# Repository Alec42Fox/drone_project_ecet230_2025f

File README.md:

# ECET - 230 - 001 - HMS (Height Maintenance System)
* video of the prototype in action (fixed to a single axis)
* Also hyperlink to simulation below:

## Goals
* Make a single propelled drone that hovers at a specific height and can get back to that height when outside forces act on it.
## Team Members
* Alec Fox - Programming
* Angelo McNeill - CAD Design
* Cristian D. Garcia S. - PCB Design
## Tools and Technologies
* Fusion 360 - 3D Design
* KiCad - PCB Design
* GitHub - Collaboration and Communication
## Timeline
| Phase | Duration | Description |
| :-------: | :------: | :-------: |
| Research Technology | Week 1 | Get the necessary electronics for the project with breakout boards and datasheets for future PCB design |
| CAD Design and Programming | Week 2 - 3 | Work on the design of the frame and chassis of the drone while working of the programming of the electronics |
| Proof of Concept | Week 4 - 5 | Use breakout boards and code to do testing and debugging |
| Looks-Like Prototype and Further Programming | Week 6 - 7 | Print the frame and chassis and do test to make sure they work well; also some programming on the side |
| PCB Design and Manufacturing | Week 8 - 9 | Make the PCB board that will have all the electronics and also buy it |
| Works-Like Prototype  | Week 10 | Test that the code works as intended |
| Engineering Prototype | Week 11 - 12 | Make the final prototype while testing and debugging; combining the looks-like and works-like prototypes|
## License
* The project uses an MIT license so our project is open-source. We do ask for attribution.

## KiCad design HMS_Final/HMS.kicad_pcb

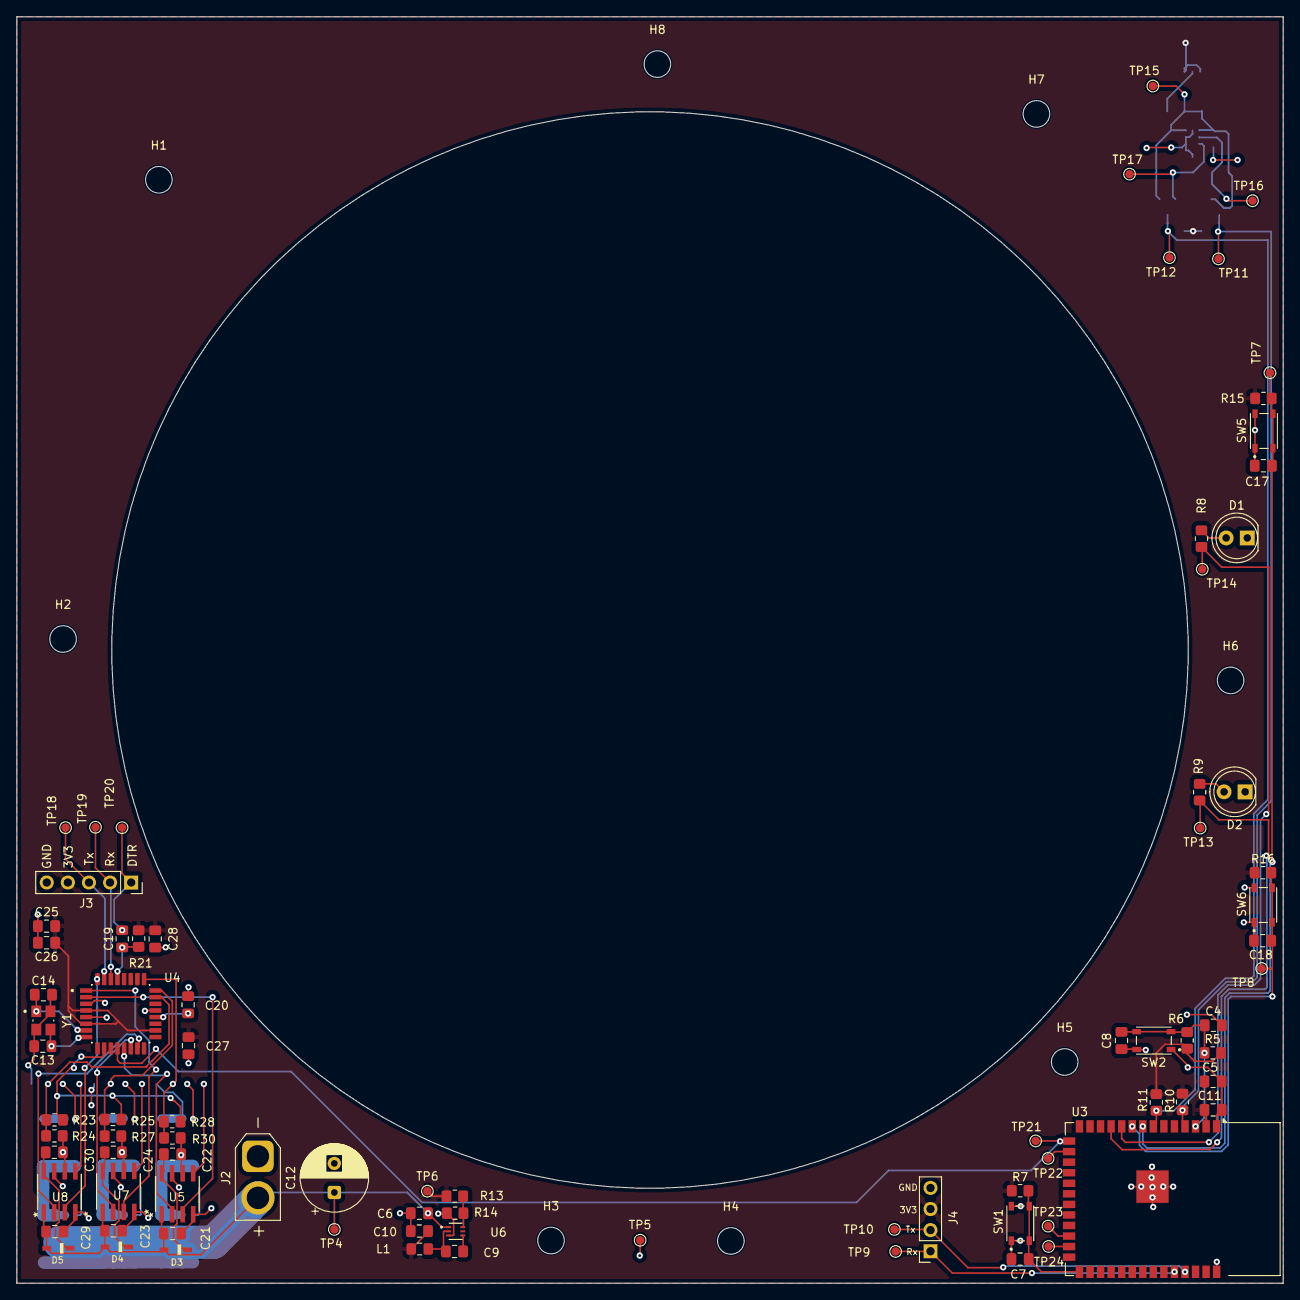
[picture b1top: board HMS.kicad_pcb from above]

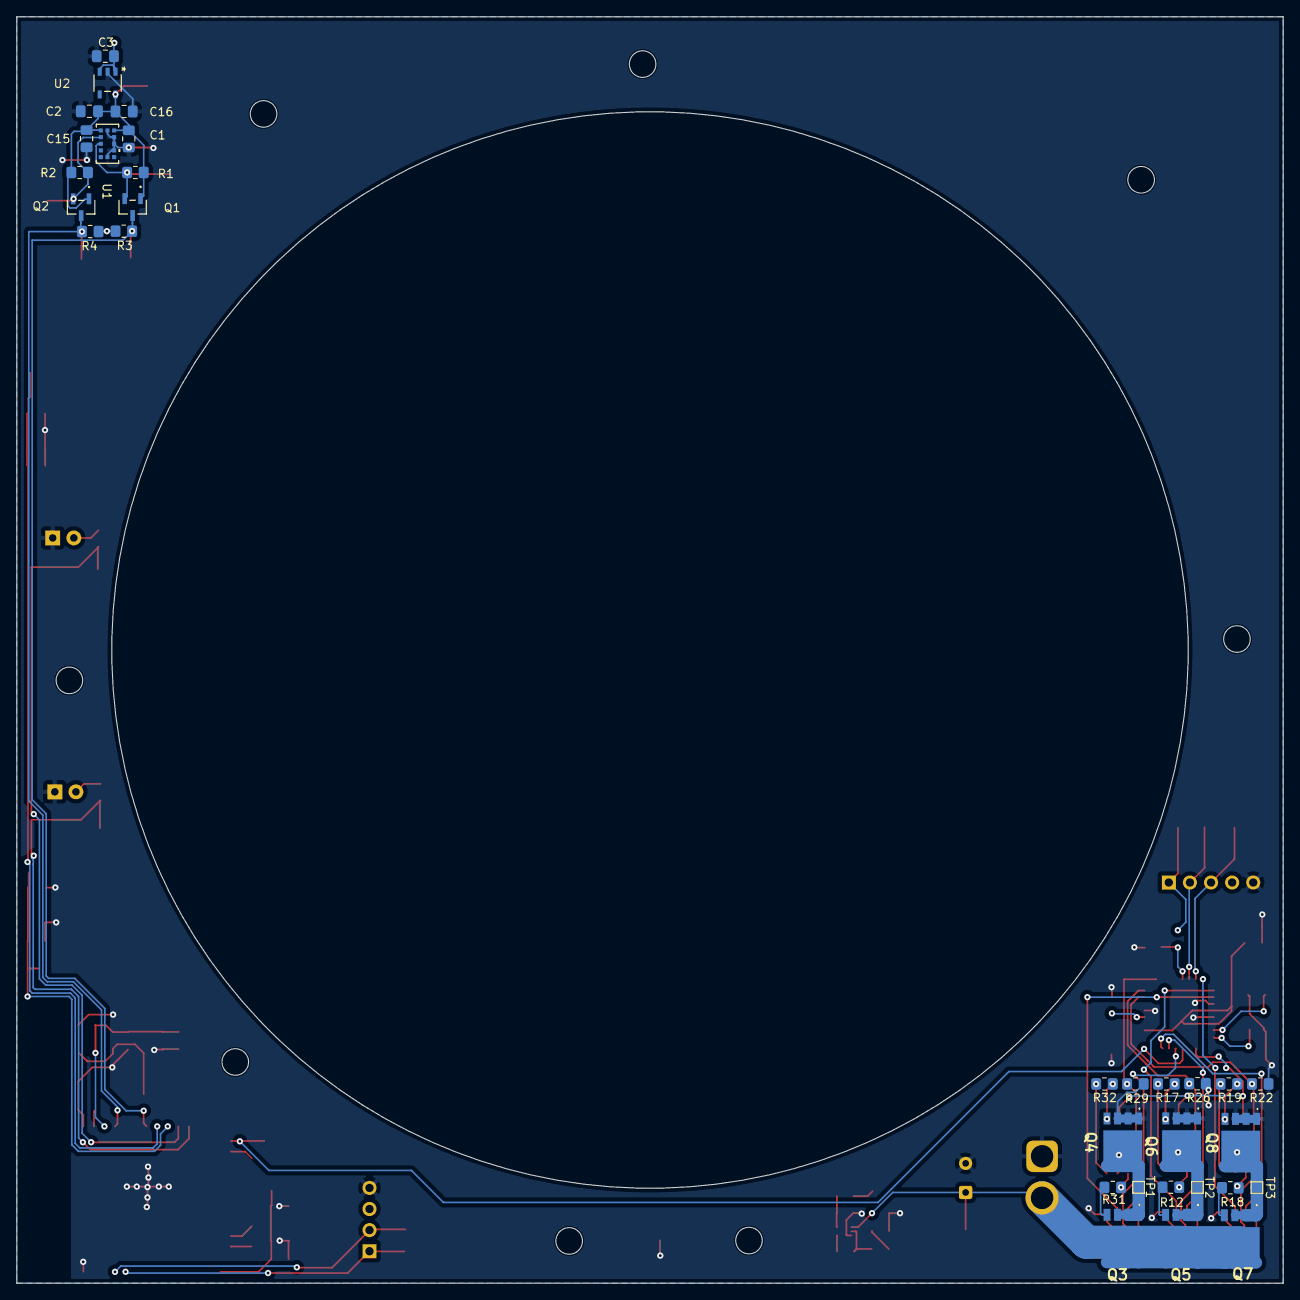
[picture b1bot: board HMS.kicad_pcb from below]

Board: 2 copper layers, 152.4 x 152.4 mm, 123 parts (31 on the bottom side), 60 nets.

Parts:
C1, C5, C7, C8, C9, C15, C17, C18, C19, C20, C25, C26, C27: 0.1 uF; C_0805_2012Metric_Pad1.18x1.45mm_HandSolder
C2, C3, C6, C21, C23, C29: 10 uF; C_0805_2012Metric_Pad1.18x1.45mm_HandSolder
C4: 1 uF; C_0805_2012Metric_Pad1.18x1.45mm_HandSolder
C10: 22 uF; C_0805_2012Metric_Pad1.18x1.45mm_HandSolder
C11, C16, C28: 4.7 uF; C_0805_2012Metric_Pad1.18x1.45mm_HandSolder
C12: 1000 uF; CP_Radial_D8.0mm_P3.50mm
C13, C14: 18 pF; C_0805_2012Metric_Pad1.18x1.45mm_HandSolder
C22, C24, C30: 2.2 uF; C_0805_2012Metric_Pad1.18x1.45mm_HandSolder
D1: RED; LED_D5.0mm
D2: GREEN; LED_D5.0mm
D3, D4, D5: 1N4148WS; SODFL2512X100N
H1, H2, H3, H4, H5, H6, H7, H8: MountingHole; MountingHole_3.2mm_M3
J2: 15V Input; AMASS_XT30U-F_1x02_P5.0mm_Vertical
J3: Conn_01x05_Socket; PinSocket_1x05_P2.54mm_Vertical
J4: Conn_01x04_Socket; PinSocket_1x04_P2.54mm_Vertical
L1: 3.3 uH; L_0805_2012Metric_Pad1.15x1.40mm_HandSolder
Q1, Q2: BSS138; SOT-23-3_1P4X3P040_ONS
Q3, Q4, Q5, Q6, Q7, Q8: TPH1R403NL,L1Q; TPH1R403NLL1Q
R1, R2, R3, R4, R5, R6, R7, R14, R15, R16, R21, R22, R26, R29: 10 K; R_0805_2012Metric_Pad1.20x1.40mm_HandSolder
R8: 62.5; R_0805_2012Metric_Pad1.20x1.40mm_HandSolder
R9: 60; R_0805_2012Metric_Pad1.20x1.40mm_HandSolder
R10, R11: 4.7 K; R_0805_2012Metric_Pad1.20x1.40mm_HandSolder
R12, R17, R18, R19, R31, R32: 100; R_0805_2012Metric_Pad1.20x1.40mm_HandSolder
R13: 31.6 K; R_0805_2012Metric_Pad1.20x1.40mm_HandSolder
R23, R24, R25, R27, R28, R30: 33 K; R_0805_2012Metric_Pad1.20x1.40mm_HandSolder
SW1, SW2, SW5, SW6: PTS810_SJM_250_SMTR_LFS; SW_PTS810_SJM_250_SMTR_LFS
TP1, TP2, TP3: TestPoint_Small; TestPoint_Pad_1.0x1.0mm
TP4, TP5, TP6, TP7, TP8, TP9, TP10, TP11, TP12, TP13, TP14, TP15, TP16, TP17, TP18, TP19, TP20, TP21, TP22, TP23, TP24: TestPoint_Small; TestPoint_Pad_D1.0mm
U1: VL53L0CXV0DH/1; LGA12_STM
U2: MIC5255-2.8YM5-TR; SOT-23-5_M5_MCH
U3: ESP32-S3-WROOM-1
U4: ATMEGA328P-AU; QFP80P900X900X120-32N
U5, U7, U8: IR2101STRPBF; SO8N_INF
U6: AP62150Z6-7; SOT563_DIO
Y1: ABM8G-16.000MHZ-18-D2Y-T; XTAL_ABM8G-16.000MHZ-18-D2Y-T

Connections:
/BuckRegulator/3V3: C3.1, C5.1, C10.2, C11.1, C25.1, C26.1, C27.2, C28.1, J3.4, J4.3, L1.2, R3.1, R4.1, R5.1, R6.1, R7.1, R10.1, R11.1, R13.1, R15.1, R16.1, R21.2, TP6.1, U2.1 (IN), U2.3 (EN), U3.2 (3V3), U4.4 (VCC), U4.6 (VCC__1), U4.18 (AVCC)
/BuckRegulator/Battery: C6.1, C12.1, C21.1, C23.1, C29.1, D3.2 (A), D4.2 (A), D5.2 (A), J2.2, Q3.5 (D_1), Q3.6 (D_2), Q3.7 (D_3), Q3.8 (D_4), Q3.9 (D_5), Q5.5 (D_1), Q5.6 (D_2), Q5.7 (D_3), Q5.8 (D_4), Q5.9 (D_5), Q7.5 (D_1), Q7.6 (D_2), Q7.7 (D_3), Q7.8 (D_4), Q7.9 (D_5), TP4.1, U5.1 (VCC), U6.1 (VIN), U7.1 (VCC), U8.1 (VCC)
/Buttons/Hover: C17.1, R15.2, SW5.3, SW5.4, TP7.1, U3.8 (IO15)
/Buttons/Land: C18.1, R16.2, SW6.3, SW6.4, TP8.1, U3.9 (IO16)
/Distance/2V8: C1.1, C2.1, C15.1, C16.1, Q1.1 (G), Q2.1 (G), R1.1, R2.1, TP15.1, U1.1 (AVDDVCSEL), U1.11 (AVDD), U2.5 (OUT)
/Distance/SCL: Q2.3 (D), R4.2, R10.2, TP11.1, U3.4 (IO4)
/Distance/SCL_2.8 V: Q2.2 (S), R2.2, TP16.1, U1.10 (SCL)
/Distance/SDA: Q1.3 (D), R3.2, R11.2, TP12.1, U3.7 (IO7)
/Distance/SDA_2.8 V: Q1.2 (S), R1.2, TP17.1, U1.9 (SDA)
/LED/GREEN LED: R9.1, TP13.1, U3.11 (IO18)
/LED/RED LED: R8.1, TP14.1, U3.10 (IO17)
/Microcontorller/PWM: TP21.1, U3.15 (IO3), U4.12 (PB0)
/Microcontorller/Rx: J4.1, TP9.1, U3.36 (RXD0)
/Microcontorller/Tx: J4.2, TP10.1, U3.37 (TXD0)
/Microcontorller/~BOOT: C7.1, R7.2, SW1.3, SW1.4, U3.27 (IO0)
/Microcontorller/~RESET: C4.1, C8.1, R5.2, R6.2, SW2.3, SW2.4, U3.3 (EN)
/MotorDriver/AH: U4.13 (PB1), U5.2 (HIN)
/MotorDriver/AL: U4.2 (PD4), U5.3 (LIN)
/MotorDriver/BH: U4.14 (PB2), U7.2 (HIN)
/MotorDriver/BL: U4.1 (PD3), U7.3 (LIN)
/MotorDriver/CH: U4.15 (PB3), U8.2 (HIN)
/MotorDriver/CL: U4.32 (PD2), U8.3 (LIN)
/MotorDriver/COMMON: R23.1, R25.1, R28.1, U4.10 (PD6)
/MotorDriver/DTR: C19.1, J3.1, TP20.1
/MotorDriver/GHA: R31.1, U5.7 (HO)
/MotorDriver/GHB: R12.1, U7.7 (HO)
/MotorDriver/GHC: R18.1, U8.7 (HO)
/MotorDriver/GLA: R32.1, U5.5 (LO)
/MotorDriver/GLB: R17.1, U7.5 (LO)
/MotorDriver/GLC: R19.1, U8.5 (LO)
/MotorDriver/PHASEA: C22.1, Q3.1 (S_1), Q3.2 (S_2), Q3.3 (S_3), Q4.5 (D_1), Q4.6 (D_2), Q4.7 (D_3), Q4.8 (D_4), Q4.9 (D_5), R30.2, TP1.1, U5.6 (VS)
/MotorDriver/PHASEB: C24.1, Q5.1 (S_1), Q5.2 (S_2), Q5.3 (S_3), Q6.5 (D_1), Q6.6 (D_2), Q6.7 (D_3), Q6.8 (D_4), Q6.9 (D_5), R27.2, TP2.1, U7.6 (VS)
/MotorDriver/PHASEC: C30.1, Q7.1 (S_1), Q7.2 (S_2), Q7.3 (S_3), Q8.5 (D_1), Q8.6 (D_2), Q8.7 (D_3), Q8.8 (D_4), Q8.9 (D_5), R24.2, TP3.1, U8.6 (VS)
/MotorDriver/Rx: J3.2, TP19.1, U4.30 (PD0)
/MotorDriver/SensingA: R28.2, R29.1, R30.1, U4.25 (PC2)
/MotorDriver/SensingB: R25.2, R26.1, R27.1, U4.24 (PC1)
/MotorDriver/SensingC: R22.1, R23.2, R24.1, U4.23 (PC0)
/MotorDriver/Tx: J3.3, TP18.1, U4.31 (PD1)
/MotorDriver/~RESET: C19.2, R21.1, U4.29 (PC6/~RESET)
GNDREF: C1.2, C2.2, C3.2, C4.2, C5.2, C6.2, C7.2, C8.2, C10.1, C11.2, C12.2, C13.2, C14.2, C15.2, C16.2, C17.2, C18.2, C20.2, C21.2, C23.2, C25.2, C26.2, C27.1, C28.2, C29.2, D1.1 (K), D2.1 (K), J2.1, J3.5, J4.4, Q4.1 (S_1), Q4.2 (S_2), Q4.3 (S_3), Q6.1 (S_1), Q6.2 (S_2), Q6.3 (S_3), Q8.1 (S_1), Q8.2 (S_2), Q8.3 (S_3), R14.2, R22.2, R26.2, R29.2, SW1.1, SW1.2, SW2.1, SW2.2, SW5.1, SW5.2, SW6.1, SW6.2, TP5.1, U1.2 (AVSSVCSEL), U1.3 (GND), U1.4 (GND2), U1.6 (GND3), U1.12 (GND4), U2.2 (GND), U3.1 (GND), U3.40 (GND), U3.41 (GND), U4.3 (GND), U4.5 (GND__1), U4.21 (GND__2), U5.4 (COM), U6.3 (GND), U7.4 (COM), U8.4 (COM), Y1.2 (GND), Y1.4 (GND__1)
unnamed: D1.2 (A), R8.2
unnamed: D2.2 (A), R9.2
unnamed: C22.2, D3.1 (K), U5.8 (VB)
unnamed: C24.2, D4.1 (K), U7.8 (VB)
unnamed: C30.2, D5.1 (K), U8.8 (VB)
unnamed: Q3.4 (G), R31.2
unnamed: Q4.4 (G), R32.2
unnamed: Q5.4 (G), R12.2
unnamed: Q6.4 (G), R17.2
unnamed: Q7.4 (G), R18.2
unnamed: Q8.4 (G), R19.2
unnamed: TP22.1, U3.16 (IO46)
unnamed: TP23.1, U3.24 (IO47)
unnamed: TP24.1, U3.25 (IO48)
unnamed: C20.1, U4.20 (AREF)
unnamed: C14.1, U4.7 (PB6), Y1.1
unnamed: C13.1, U4.8 (PB7), Y1.3
unnamed: C9.1, U6.4 (BST)
unnamed: R13.2, R14.1, U6.6 (FB)
unnamed: C9.2, L1.1, U6.2 (SW)

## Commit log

2025-09-15 Delete Design Decisions.pdf
    Updating with new file.
2025-09-15 Delete Project Definition.pdf
    Updating with new file
2025-11-13 Add files via upload
    PID loop code, tested it works on the actual motor and esc, proof of concept
2025-12-12 Most up-to-date version of PID code
    Most up-to-date version of PID code
    implements a PID controller for a distance-sensing application using an ESP32,
    designed to make the drone hover at a fixed distance
2025-12-17 Rename HMS.zip to HMS_Rough.zip
2025-12-17 Rename PID_Dec12.ino to PID_Rough.ino
2025-12-17 Create test
2025-12-17 Rename Bill of Materials - POC.pdf to Proof_of_Concept/Bill of Materials - POC.pdf
2025-12-17 Rename Design Decisions - POC.pdf to Proof_of_Concept/Design Decisions - POC.pdf
2025-12-17 Rename POC.ino to Proof_of_Concept/POC.ino
2025-12-17 Rename Bill_of_Materials_Final.pdf to Final/Bill_of_Materials_Final.pdf
2025-12-17 Rename Block_Diagram_Final.pdf to Final/Block_Diagram_Final.pdf
2025-12-17 Rename Design_Decisions_Final.pdf to Final/Design_Decisions_Final.pdf
2025-12-17 Rename HMS_Final_Code.ino to Final/HMS_Final_Code.ino
2025-12-17 Rename Logbook.pdf to Project_Documents/Logbook.pdf
2025-12-17 Rename Project_Definition.pdf to Project_Documents/Project_Definition.pdf
2025-12-17 Rename Prototype_Plan.pdf to Project_Documents/Prototype_Plan.pdf
2025-12-17 Rename Testing_Document.pdf to Project_Documents/Testing_Document.pdf
2025-12-17 Rename User_Documentation.pdf to Project_Documents/User_Documentation.pdf
2025-12-17 Rename PID_Rough.ino to Proof_of_Concept/PID_Rough.ino
2025-12-19 Add embedded YouTube video link to README
2025-12-19 Add embedded YouTube video to README
    Updated README to include an embedded YouTube video. (and fixed previous attempt)
2025-12-19 Update video embed to thumbnail link
    Replaced video iframe with a clickable thumbnail link.
2025-12-19 Add video link of prototype in action
    Added a video link demonstrating the prototype's functionality.
2025-12-19 Add video and CodePen links to README
    Added hyperlinks to video and CodePen project.
2025-12-19 Update project attribution in README
